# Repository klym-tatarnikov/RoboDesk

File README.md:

# RoboDesk
Read LOGICDATA protocol to control height of a powered sit/stand desk.

LOGICDATA protocol decoding from [phord's RoboDesk](https://github.com/phord/RoboDesk/tree/LogicData)

## Current features:
* Double tap a direction to go to a hardcoded target height
* Wifi connection
* MQTT publish/subscribe

## Files:
* `firmware`: platformio code for the d1 mini
* `schematic`: Eagle schematic/board/gerbers

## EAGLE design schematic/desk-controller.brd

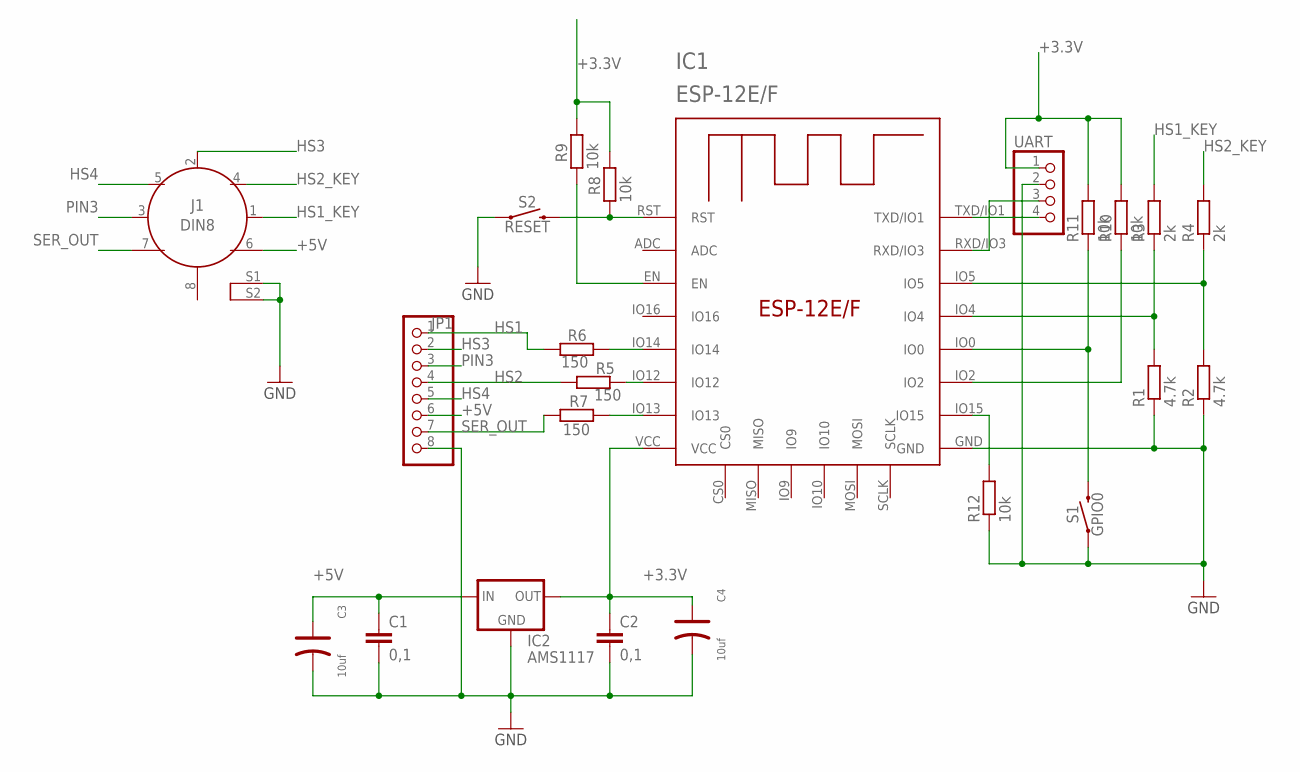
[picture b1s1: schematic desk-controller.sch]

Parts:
C1, C2: 0,1; C1206
C3, C4: 10uf; AVX-B
IC1: ESP-12E/F; ESP-12E
IC2: AMS1117; SOT223
J1: DIN8; DIN8-RA-PTH
JP1: PINHD-1X8; 1X08
R1, R2: 4.7k; R0805
R3, R4: 2k; R0805
R5, R6, R7: 150; R0805
R8, R9, R10, R11, R12: 10k; R0805
S1: GPIO0; TACTILE_SWITCH_PTH_RIGHT_ANGLE_KIT
S2: RESET; TACTILE_SWITCH_PTH_RIGHT_ANGLE_KIT
UART: PINHD-1X4; 1X04

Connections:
+3.3V: C2.1, C4.+, IC1.VCC, IC2.2 (OUT), R8.1, R9.1, R10.2, R11.2, UART.1
+5V: C1.1, C3.+, IC2.3 (IN), J1.6, JP1.6
GND: C1.2, C2.2, C3.-, C4.-, IC1.GND, IC2.1 (GND), J1.S1 (SHIELD), J1.S2 (SHIELD), JP1.8, R1.1, R2.1, R12.1, S1.1, S2.1, UART.2
HS1: JP1.1, R6.2
HS1_KEY: J1.1, R3.2
HS2: JP1.4, R5.2
HS2_KEY: J1.4, R4.2
HS3: J1.2, JP1.2
HS4: J1.5, JP1.5
unnamed: IC1.IO14, R6.1
unnamed: IC1.IO12, R5.1
unnamed: IC1.IO4, R1.2, R3.1
unnamed: IC1.IO5, R2.2, R4.1
unnamed: IC1.TXD/IO1, UART.4
unnamed: IC1.IO13, R7.1
unnamed: IC1.RST, R8.2, S2.2
unnamed: IC1.EN, R9.2
unnamed: IC1.IO2, R10.1
unnamed: IC1.IO0, R11.1, S1.2
unnamed: IC1.RXD/IO3, UART.3
unnamed: IC1.IO15, R12.2
PIN3: J1.3, JP1.3
SER_OUT: J1.7, JP1.7, R7.2

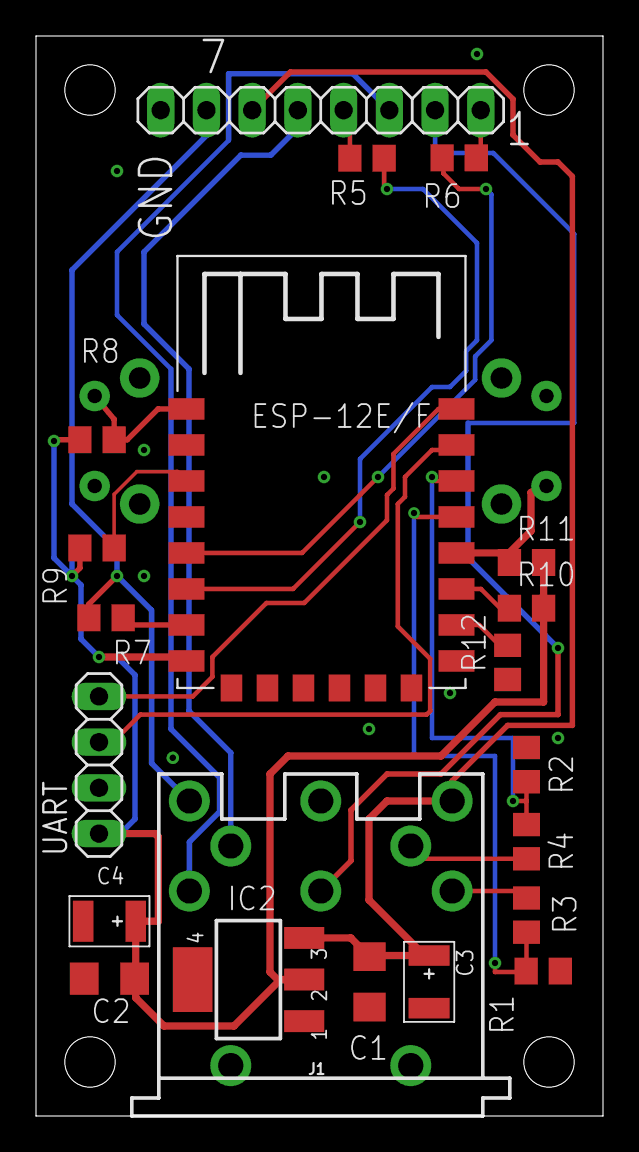
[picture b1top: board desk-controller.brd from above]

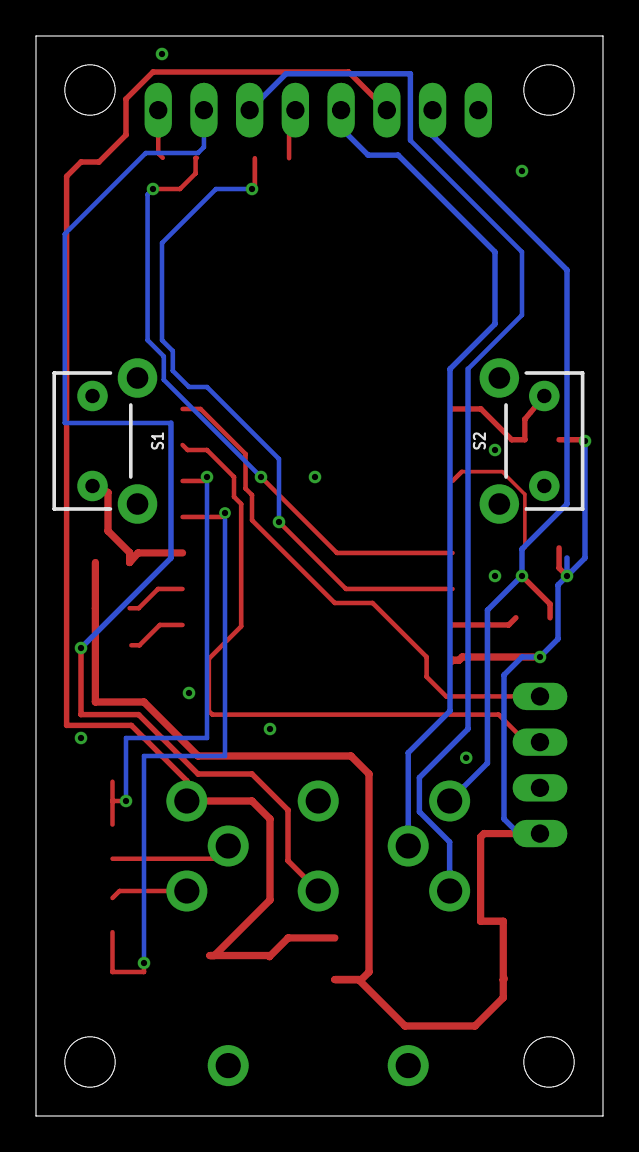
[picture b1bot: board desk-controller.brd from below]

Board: 2 copper layers, 31.5 x 60.0 mm, 23 parts (2 on the bottom side), 23 nets.

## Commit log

2019-11-27 add schematic
2020-01-14 docs: add gimp file for the logicdata controller
    Doesn't fit anywhere, so it might as well go here.
2020-01-14 reorg; update readme+license
2020-01-14 feat(schematic): Redo schematic to new design
2020-01-14 feat(firmware): switch firmware to pio; rewrite buttons
2020-01-14 fix(enclosure): cleanup scad; tweak sizes
    I changed the front hole sizes to fit what I think is correct, but I
    just carved out the holes till they fit on the thing I printed.
2021-08-11 Wifi + MQTT
    Added WiFi + MQTT
2021-08-11 Added Eagle schematics

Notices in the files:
parts and their libraries:
SparkFun-Switches: Licensing: Creative Commons ShareAlike 4.0 International - https://creativecommons.org/licenses/by-sa/4.0
